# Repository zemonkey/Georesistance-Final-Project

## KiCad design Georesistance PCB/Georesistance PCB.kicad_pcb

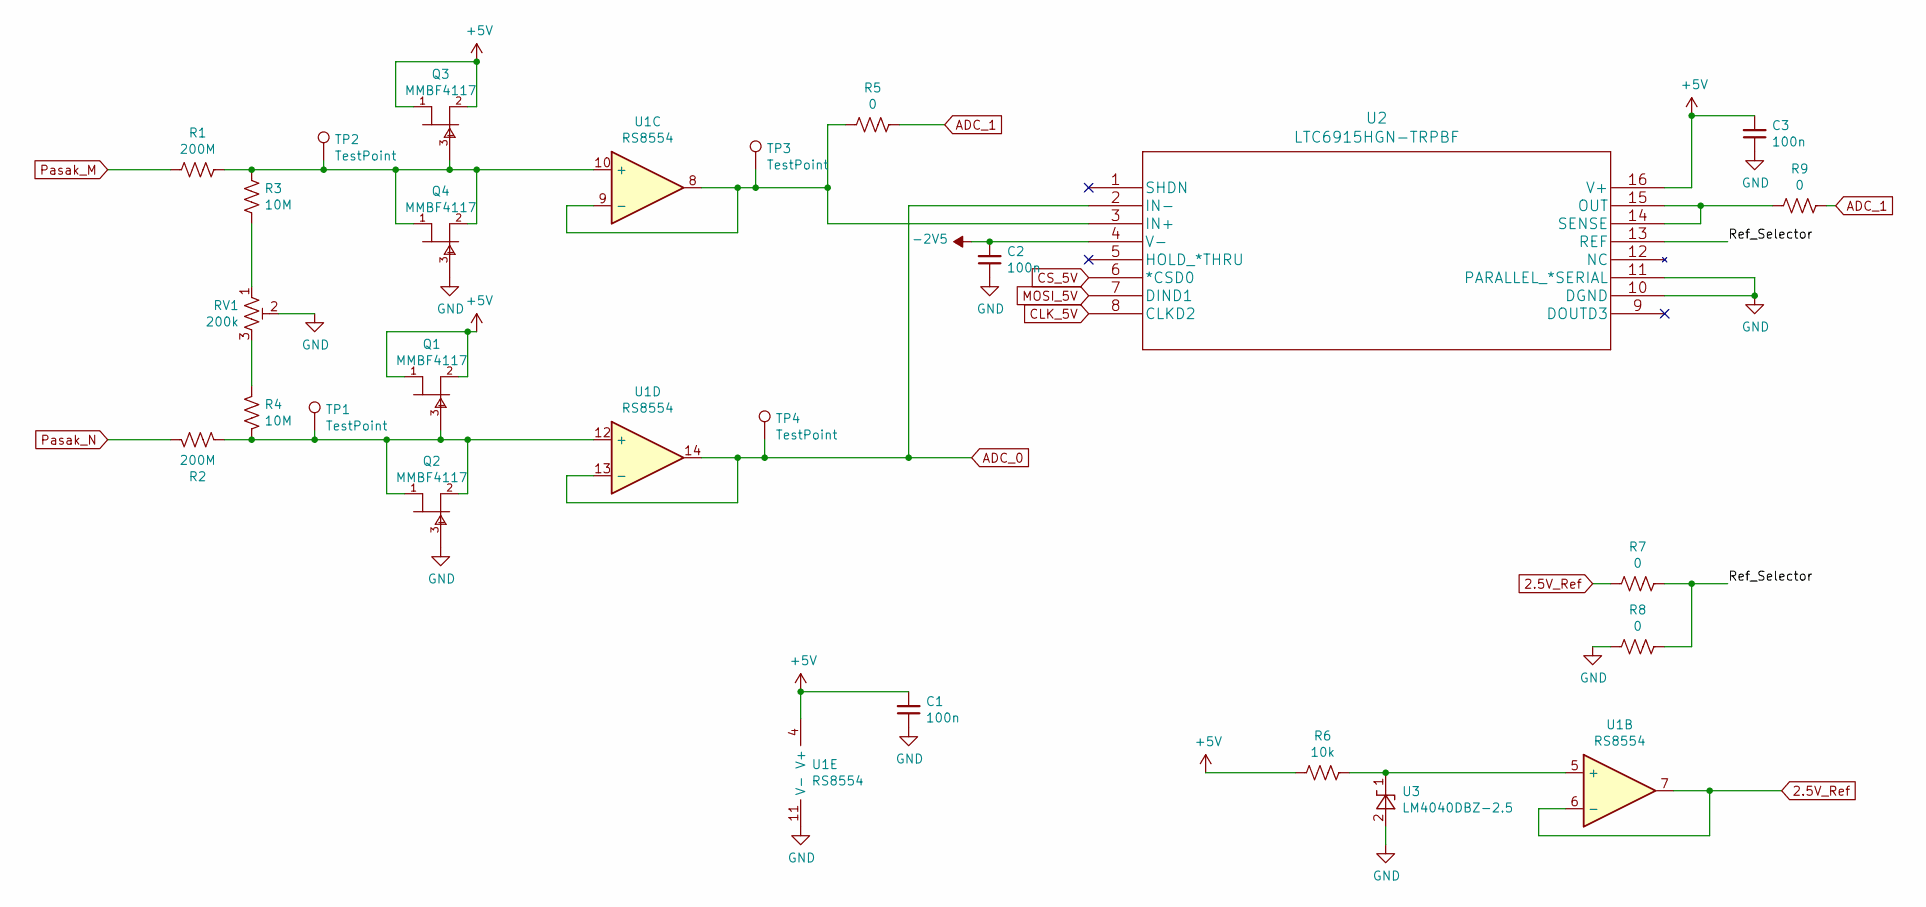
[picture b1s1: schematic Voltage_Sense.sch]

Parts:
C1, C2, C3: 100n; C_0402_1005Metric_Pad0.74x0.62mm_HandSolder
Q1, Q2, Q3, Q4: MMBF4117; ON_Semi-31808-0-0-0; mouser part number 512-MMBF4117; digikey description JFET N-CH 40V 0.225W SOT23
R1, R2: 200M; R_Axial_DIN0414_L11.9mm_D4.5mm_P15.24mm_Horizontal
R3, R4: 10M; R_Axial_DIN0207_L6.3mm_D2.5mm_P7.62mm_Horizontal
R5, R7, R8, R9: 0; R_0402_1005Metric_Pad0.72x0.64mm_HandSolder
R6: 10k; R_Axial_DIN0207_L6.3mm_D2.5mm_P7.62mm_Horizontal
RV1: 200k; Potentiometer_ACP_CA9-H5_Horizontal
TP1, TP2, TP3, TP4: TestPoint; TestPoint_THTPad_D1.0mm_Drill0.5mm
U1: RS8554; SOIC-14_3.9x8.7mm_P1.27mm
U2: LTC6915HGN-TRPBF; SSOP-16_3.9x4.9mm_P0.635mm
U3: LM4040DBZ-2.5; SOT-23

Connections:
2.5V_Ref: R7.2, U1.6 (-), U1.7
+5V: C1.2, C3.2, Q1.1 (D), Q1.2 (S), Q3.1 (D), Q3.2 (S), R6.2, U1.4 (V+), U2.16 (V+); also elsewhere on the board
-2V5: C2.2, U2.4 (V-); also elsewhere on the board
/Voltage_Sense/Ref_Selector: R7.1, R8.1, U2.13 (REF)
ADC_0: TP4.1, U1.13 (-), U1.14, U2.2 (IN-); also elsewhere on the board
ADC_1: R5.1, R9.1; also elsewhere on the board
CLK_5V: U2.8 (CLKD2); also elsewhere on the board
CS_5V: U2.6 (*CSD0); also elsewhere on the board
GND: C1.1, C2.1, C3.1, Q2.3 (G), Q4.3 (G), R8.2, RV1.2, U1.11 (V-), U2.10 (DGND), U2.11 (PARALLEL_*SERIAL), U3.2 (A); also elsewhere on the board
MOSI_5V: U2.7 (DIND1); also elsewhere on the board
unnamed: Q1.3 (G), Q2.1 (D), Q2.2 (S), R2.1, R4.2, TP1.1, U1.12 (+)
unnamed: Q3.3 (G), Q4.1 (D), Q4.2 (S), R1.1, R3.2, TP2.1, U1.10 (+)
unnamed: R3.1, RV1.1
unnamed: R4.1, RV1.3
unnamed: R5.2, TP3.1, U1.8, U1.9 (-), U2.3 (IN+)
unnamed: R6.1, U1.5 (+), U3.1 (K)
unnamed: R9.2, U2.14 (SENSE), U2.15 (OUT)
Pasak_M: R1.2; also elsewhere on the board
Pasak_N: R2.2; also elsewhere on the board

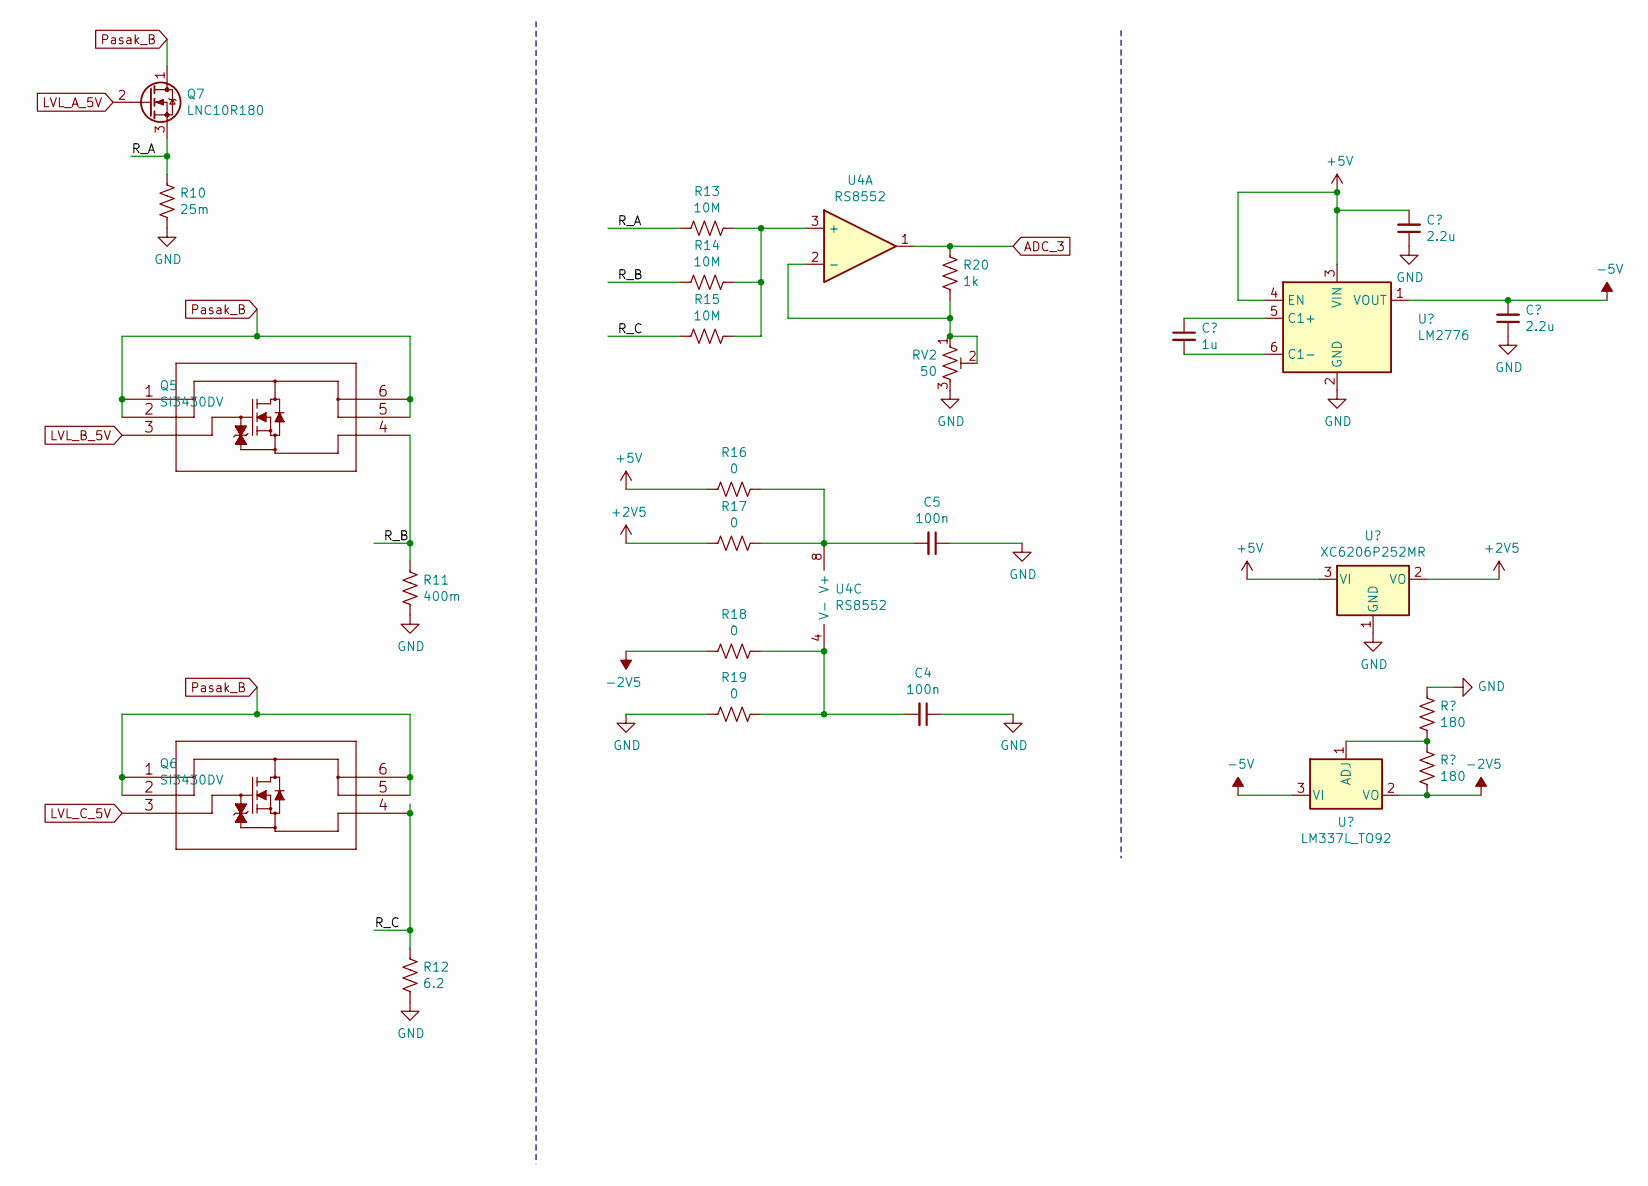
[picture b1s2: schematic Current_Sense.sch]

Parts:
C4, C5: 100n; C_0402_1005Metric_Pad0.74x0.62mm_HandSolder
Q5, Q6: SI3430DV; TSOP-6_1.65x3.05mm_P0.95mm
Q7: LNC10R180; TO-220-3_Vertical
R10: 25m; R_0603_1608Metric_Pad0.98x0.95mm_HandSolder
R11: 400m; R_2512_6332Metric_Pad1.40x3.35mm_HandSolder
R12: 6.2; R_0805_2012Metric_Pad1.20x1.40mm_HandSolder
R13, R14, R15: 10M; R_Axial_DIN0207_L6.3mm_D2.5mm_P7.62mm_Horizontal
R16, R17, R18, R19: 0; R_0402_1005Metric_Pad0.72x0.64mm_HandSolder
R20: 1k; R_Axial_DIN0207_L6.3mm_D2.5mm_P7.62mm_Horizontal
RV2: 50; Potentiometer_Bourns_3266W_Vertical
U4: RS8552; MSOP-8_3x3mm_P0.65mm

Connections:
+2V5: R17.2; also elsewhere on the board
+5V: R16.2; also elsewhere on the board
-2V5: R18.2; also elsewhere on the board
/Current_Sense/R_A: Q7.3 (S), R10.1, R13.2
/Current_Sense/R_B: Q5.4, R11.1, R14.2
/Current_Sense/R_C: Q6.4, R12.1, R15.2
ADC_3: R20.1, U4.1; also elsewhere on the board
GND: C4.1, C5.1, R10.2, R11.2, R12.2, R19.2, RV2.3; also elsewhere on the board
LVL_A_5V: Q7.2 (G); also elsewhere on the board
LVL_B_5V: Q5.3; also elsewhere on the board
LVL_C_5V: Q6.3; also elsewhere on the board
unnamed: C4.2, R18.1, R19.1, U4.4 (V-)
unnamed: C5.2, R16.1, R17.1, U4.8 (V+)
unnamed: R13.1, R14.1, R15.1, U4.3 (+)
unnamed: R20.2, RV2.1, RV2.2, U4.2 (-)
Pasak_B: Q5.1, Q5.2, Q5.5, Q5.6, Q6.1, Q6.2, Q6.5, Q6.6, Q7.1 (D); also elsewhere on the board

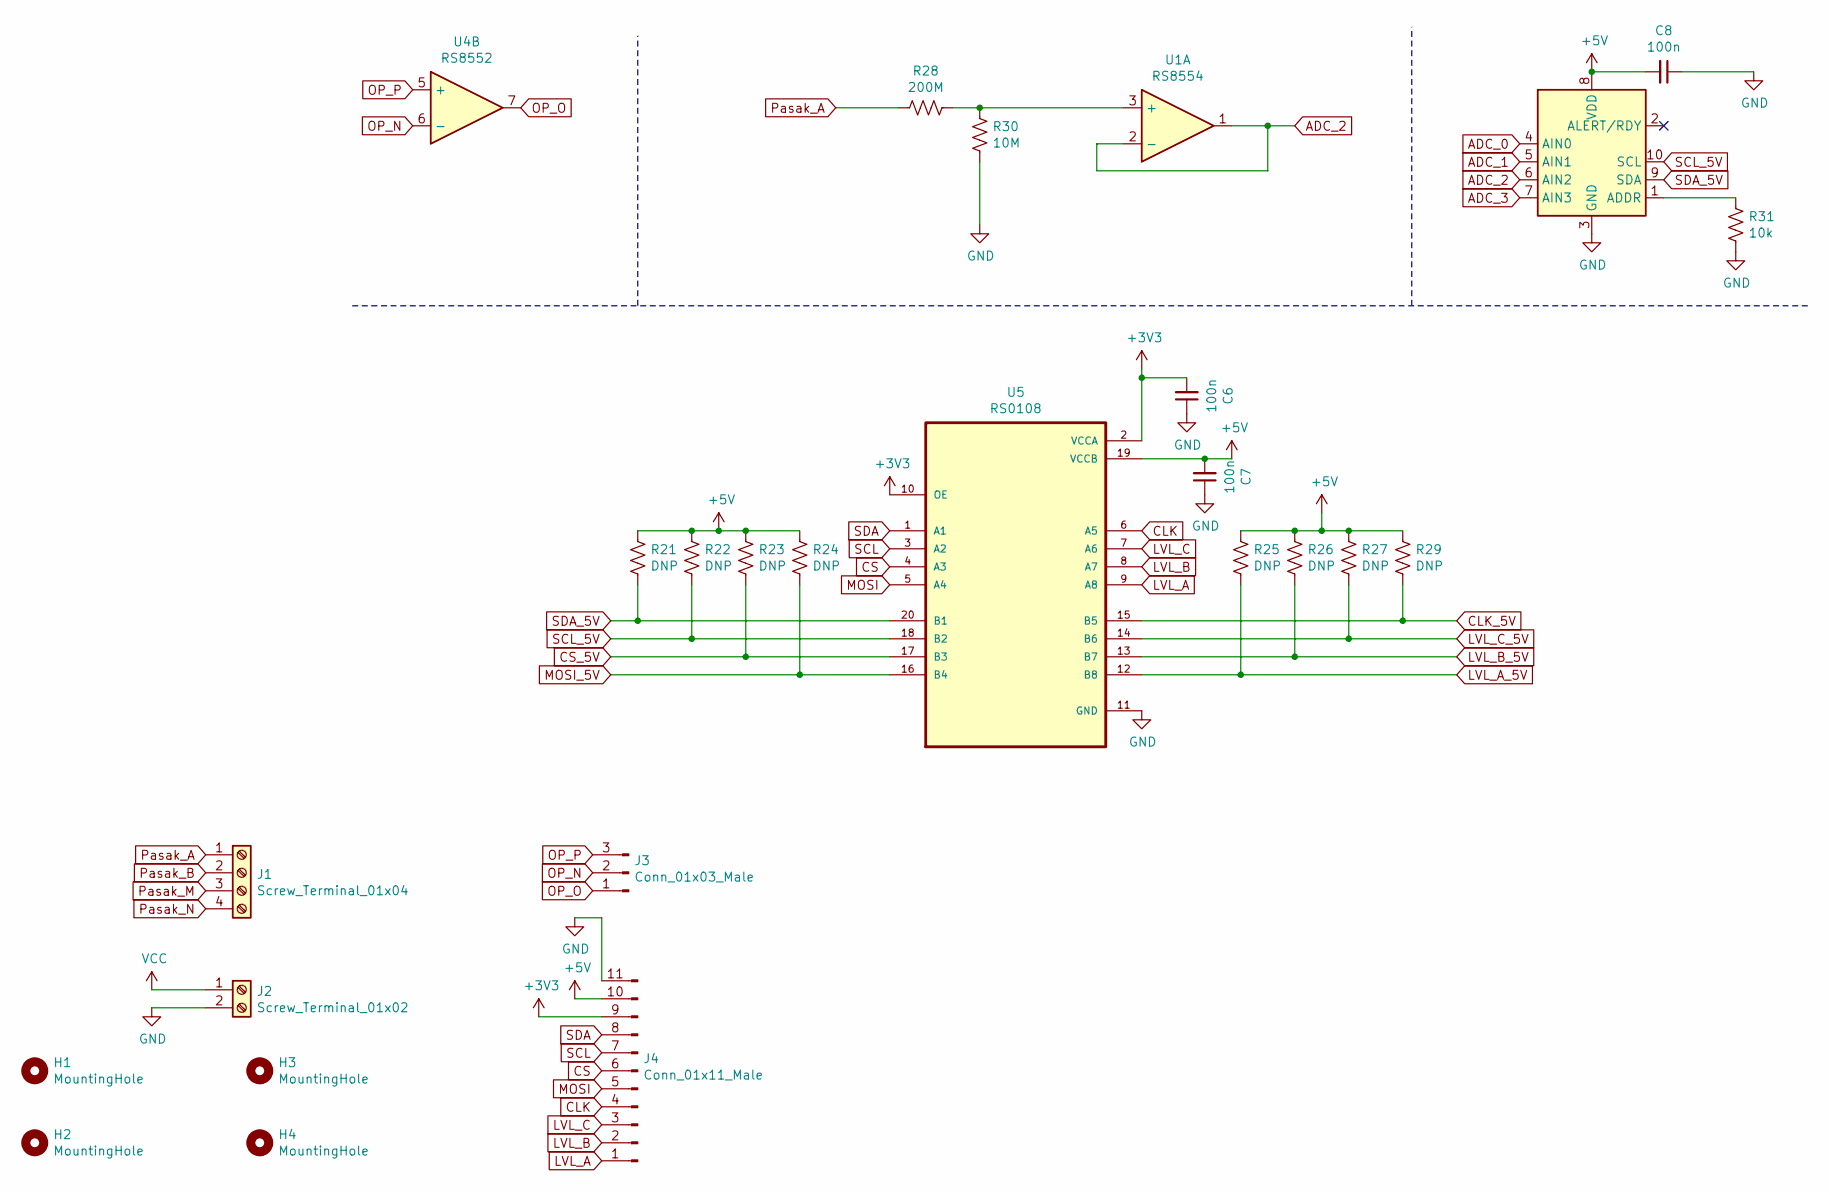
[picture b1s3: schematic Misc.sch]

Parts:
C6, C7, C8: 100n; C_0402_1005Metric_Pad0.74x0.62mm_HandSolder
H1, H2, H3, H4: MountingHole; MountingHole_3.2mm_M3_DIN965
J1: Screw_Terminal_01x04; TerminalBlock_RND_205-00014_1x04_P5.00mm_Horizontal
J2: Screw_Terminal_01x02; TerminalBlock_RND_205-00012_1x02_P5.00mm_Horizontal
J3: Conn_01x03_Male; PinSocket_1x03_P2.54mm_Vertical
J4: Conn_01x11_Male; PinHeader_1x11_P2.54mm_Vertical
R21, R22, R23, R24, R25, R26, R27, R29: DNP; R_0402_1005Metric_Pad0.72x0.64mm_HandSolder
R28: 200M; R_Axial_DIN0414_L11.9mm_D4.5mm_P15.24mm_Horizontal
R30: 10M; R_Axial_DIN0207_L6.3mm_D2.5mm_P7.62mm_Horizontal
R31: 10k; R_Axial_DIN0207_L6.3mm_D2.5mm_P7.62mm_Horizontal
U1: RS8554; SOIC-14_3.9x8.7mm_P1.27mm
U4: RS8552; MSOP-8_3x3mm_P0.65mm
U5: RS0108; SOP65P640X120-20N
U6: ADS1115IDGS; TSSOP-10_3x3mm_P0.5mm

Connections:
+3V3: C6.2, J4.9, U5.2 (VCCA), U5.10 (OE)
+5V: C7.2, C8.2, J4.10, R21.1, R22.1, R23.1, R24.1, R25.1, R26.1, R27.1, R29.1, U5.19 (VCCB), U6.8 (VDD); also elsewhere on the board
ADC_0: U6.4 (AIN0); also elsewhere on the board
ADC_1: U6.5 (AIN1); also elsewhere on the board
ADC_2: U1.1, U1.2 (-), U6.6 (AIN2)
ADC_3: U6.7 (AIN3); also elsewhere on the board
CLK: J4.4, U5.6 (A5)
CLK_5V: R29.2, U5.15 (B5); also elsewhere on the board
CS: J4.6, U5.4 (A3)
CS_5V: R23.2, U5.17 (B3); also elsewhere on the board
GND: C6.1, C7.1, C8.1, J2.2, J4.11, R30.1, R31.2, U5.11 (GND), U6.3 (GND); also elsewhere on the board
LVL_A: J4.1, U5.9 (A8)
LVL_A_5V: R25.2, U5.12 (B8); also elsewhere on the board
LVL_B: J4.2, U5.8 (A7)
LVL_B_5V: R26.2, U5.13 (B7); also elsewhere on the board
LVL_C: J4.3, U5.7 (A6)
LVL_C_5V: R27.2, U5.14 (B6); also elsewhere on the board
MOSI: J4.5, U5.5 (A4)
MOSI_5V: R24.2, U5.16 (B4); also elsewhere on the board
unnamed: R28.1, R30.2, U1.3 (+)
unnamed: R31.1, U6.1 (ADDR)
OP_N: J3.2, U4.6 (-)
OP_O: J3.1, U4.7
OP_P: J3.3, U4.5 (+)
Pasak_A: J1.1, R28.2; also elsewhere on the board
Pasak_B: J1.2; also elsewhere on the board
Pasak_M: J1.3; also elsewhere on the board
Pasak_N: J1.4; also elsewhere on the board
SCL: J4.7, U5.3 (A2)
SCL_5V: R22.2, U5.18 (B2), U6.10 (SCL)
SDA: J4.8, U5.1 (A1)
SDA_5V: R21.2, U5.20 (B1), U6.9 (SDA)
VCC: J2.1; also elsewhere on the board

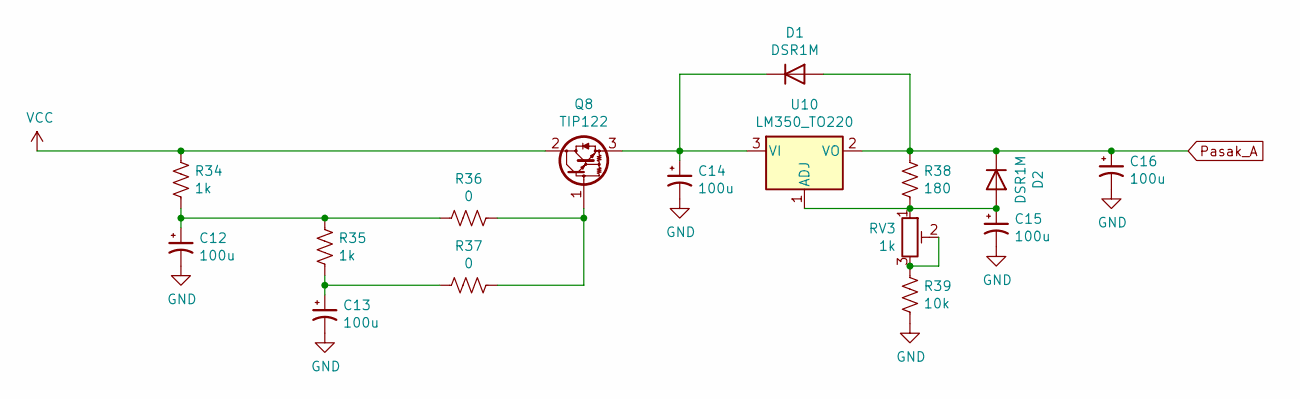
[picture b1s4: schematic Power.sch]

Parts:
C12, C13, C14, C15, C16: 100u; CP_Radial_D10.0mm_P5.00mm
D1, D2: DSR1M; D_SOD-123
Q8: TIP122; TO-220-3_Vertical
R34, R35: 1k; R_Axial_DIN0207_L6.3mm_D2.5mm_P7.62mm_Horizontal
R36, R37: 0; R_0402_1005Metric_Pad0.72x0.64mm_HandSolder
R38: 180; R_Axial_DIN0207_L6.3mm_D2.5mm_P7.62mm_Horizontal
R39: 10k; R_Axial_DIN0207_L6.3mm_D2.5mm_P7.62mm_Horizontal
RV3: 1k; Potentiometer_Bourns_3296W_Vertical
U10: LM350_TO220; TO-220-3_Vertical

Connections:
GND: C12.2, C13.2, C14.2, C15.2, C16.2, R39.2; also elsewhere on the board
unnamed: C12.1, R34.2, R35.1, R36.2
unnamed: C13.1, R35.2, R37.1
unnamed: C14.1, D1.1 (K), Q8.3 (E), U10.3 (VI)
unnamed: C15.1, D2.2 (A), R38.2, RV3.1, U10.1 (ADJ)
unnamed: Q8.1 (B), R36.1, R37.2
unnamed: R39.1, RV3.2, RV3.3
Pasak_A: C16.1, D1.2 (A), D2.1 (K), R38.1, U10.2 (VO); also elsewhere on the board
VCC: Q8.2 (C), R34.1; also elsewhere on the board

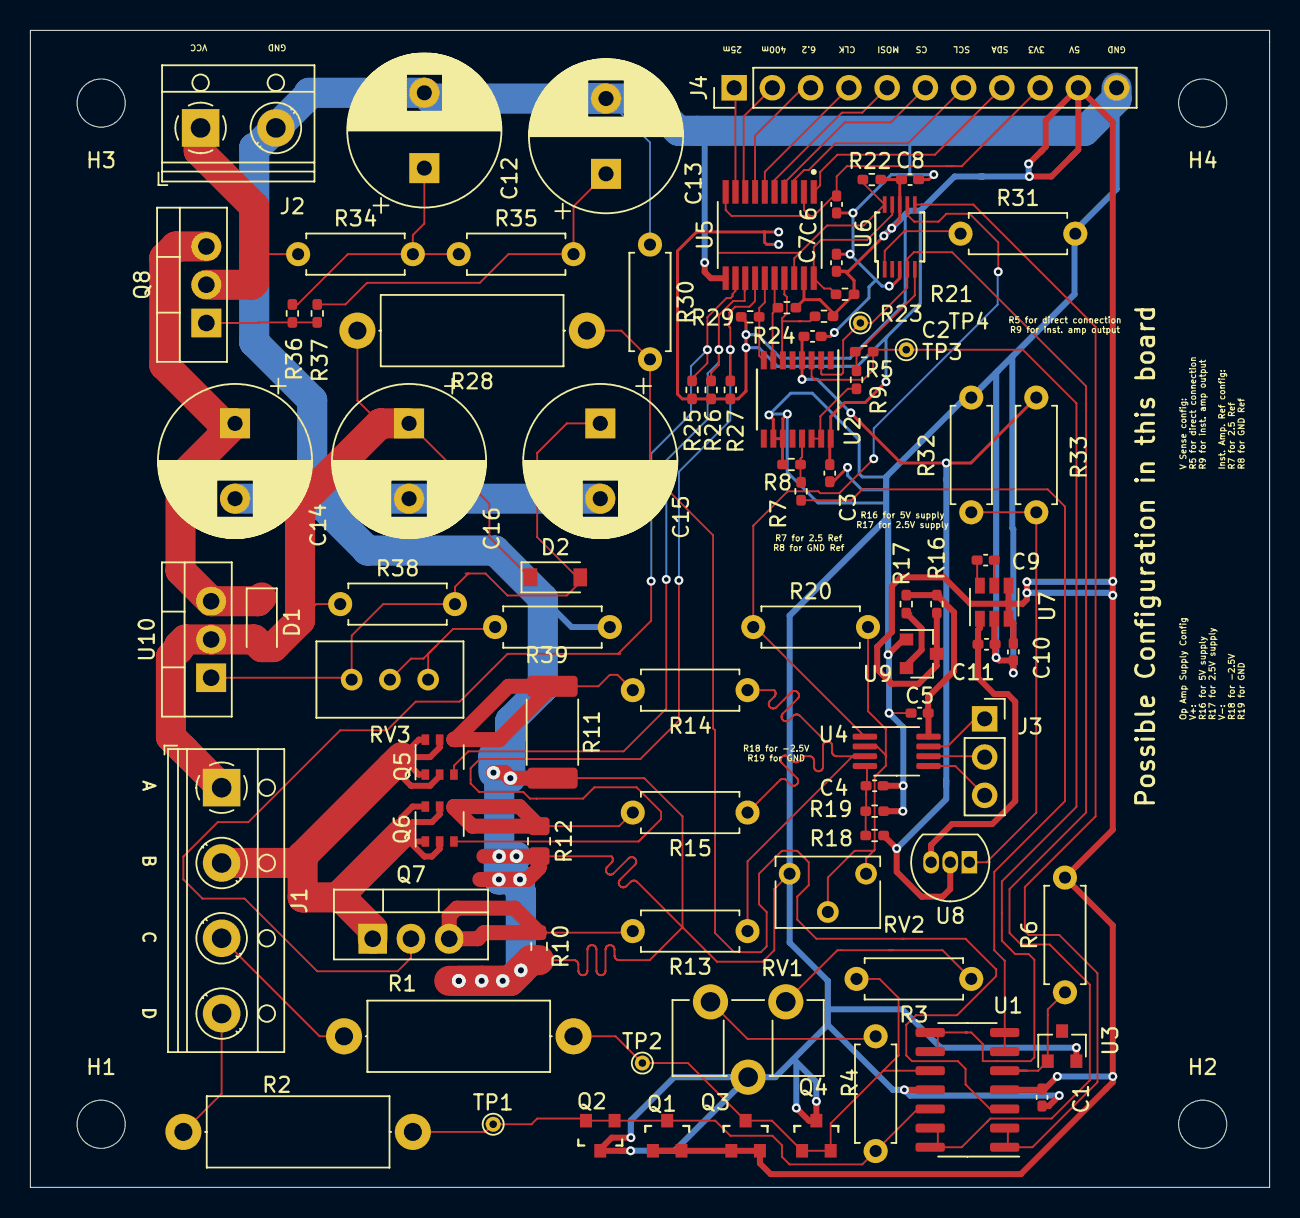
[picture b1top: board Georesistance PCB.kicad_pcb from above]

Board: 4 copper layers, 82.3 x 76.8 mm, 90 parts (0 on the bottom side), 61 nets.

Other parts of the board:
C9: 1u; C_0402_1005Metric_Pad0.74x0.62mm_HandSolder
C10, C11: 2.2u; C_0402_1005Metric_Pad0.74x0.62mm_HandSolder
R32, R33: 180; R_Axial_DIN0207_L6.3mm_D2.5mm_P7.62mm_Horizontal
U7: LM2776; SOT-23-6
U8: LM337L_TO92; TO-92_Inline
U9: AP2127N-2.5; SOT-23

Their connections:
+2V5: U9.2; also elsewhere on the board
+5V: C10.2, U7.3, U7.4, U9.3; also elsewhere on the board
-2V5: R33.2, U8.2; also elsewhere on the board
-5V: C11.2, U7.1, U8.3
GND: C10.1, C11.1, R32.1, U7.2, U9.1; also elsewhere on the board
unnamed: C9.1, U7.5
unnamed: C9.2, U7.6
unnamed: R32.2, R33.1, U8.1

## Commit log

2021-10-17 Migrated files and (hopefully) finalized the schematic
    Hopefully...
2021-10-17 Actually fixed the schematic
    Hopefully for the last time
2021-10-18 edited the PCB a little bit
2021-11-09 Added the PCB layout and simplified schematic
    deleted jumper, and fixed misconnection
2021-12-29 added things
2021-12-29 updated some parts.
    idk why this works
2022-01-01 Create INA228_Testing.ino
    added INA228
2022-01-07 added the INA228 autorange
